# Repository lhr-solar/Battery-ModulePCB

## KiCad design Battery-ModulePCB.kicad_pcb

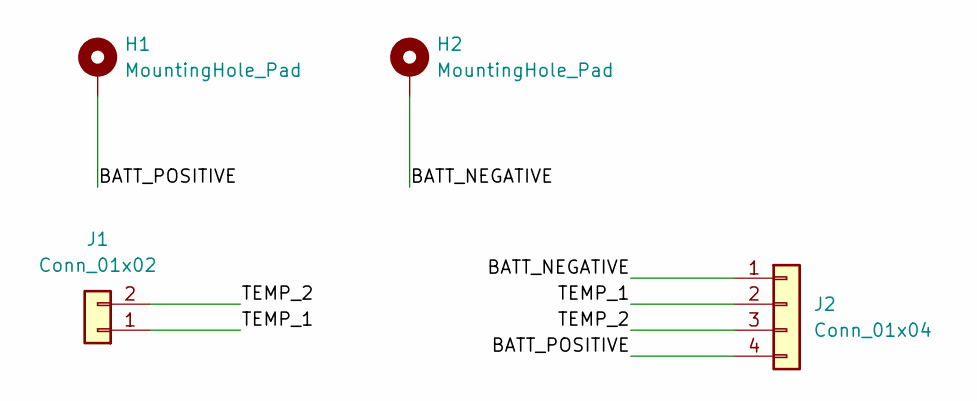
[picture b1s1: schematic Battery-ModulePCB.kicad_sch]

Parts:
H1, H2: MountingHole_Pad; MountingHole_3.2mm_M3_DIN965_Pad_TopBottom
J1: Conn_01x02; CONN_S2B-PH-K-S_JST
J2: Conn_01x04; CON_436500400_MOL

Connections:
/BATT_NEGATIVE: H2.1, J2.1
/BATT_POSITIVE: H1.1, J2.4
/TEMP_1: J1.1, J2.2
/TEMP_2: J1.2, J2.3

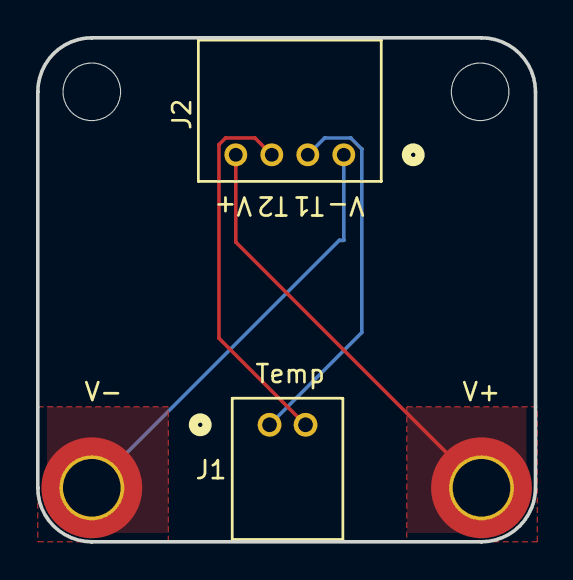
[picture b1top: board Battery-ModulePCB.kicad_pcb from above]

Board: 2 copper layers, 27.6 x 28.0 mm, 4 parts (0 on the bottom side), 4 nets.
